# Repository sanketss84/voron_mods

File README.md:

# voron mods

Building a voron printer you feel like you can add a few quality of life improvements of your own. It feels great to contribute something back so hope you find this helpful.

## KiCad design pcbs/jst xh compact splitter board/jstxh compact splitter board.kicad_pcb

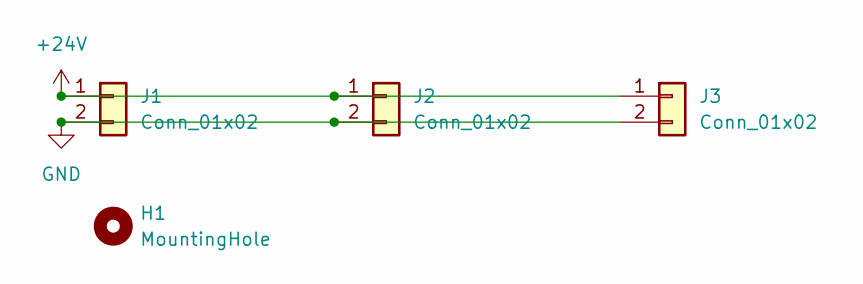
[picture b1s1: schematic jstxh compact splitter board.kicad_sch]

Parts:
H1: MountingHole; MountingHole_3.2mm_M3_ISO7380_Pad_TopBottom
J1, J2, J3: Conn_01x02; JST_XH_B2B-XH-AM_1x02_P2.50mm_Vertical

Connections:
+24V: J1.1, J2.1, J3.1
GND: J1.2, J2.2, J3.2

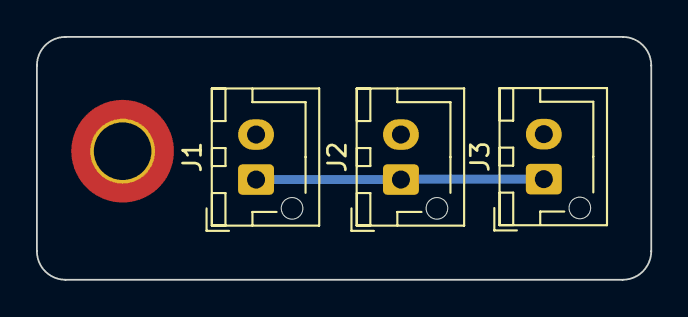
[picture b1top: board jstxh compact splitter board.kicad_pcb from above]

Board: 2 copper layers, 34.1 x 13.5 mm, 4 parts (0 on the bottom side), 2 nets.

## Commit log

2024-03-27 voron mods - pcb - jst xh splitter board
2024-03-27 added pcb images
2024-03-29 added readme for project and case to house the pcb
2024-03-29 add images to readme
2024-03-30 updated case v3 with supports
2024-03-30 fixes
2024-03-30 case v3 printed images
2024-04-11 jst xh compact splitter board
